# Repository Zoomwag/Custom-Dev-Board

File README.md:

# RP2040 Development Board

---

## Overview

This dev board is based on the Raspberry Pi RP2040 microcontroller that i deigned to learn how MCUS work
---

##  Features

- RP2040 dual-core ARM Cortex-M0+ microcontroller
- USB C interface for power and programming (much better than the picos micro usb)
- GPIO breakout for easy access
- On-board voltage regulation
- Compact and clean PCB layout

---

##  Images

### Schematic

Here you can see the schematic. I tried my best to adhere to good schemtic pratcies and i actually think that i did pretty good.

### PCB Layout

Here we can see the fully routed PCB

### 3D Model

Here you can see a 3d model of the PCB

---

---

##  Getting Started

1. Flash firmware using USB
2. Connect peripherals via GPIO
3. Start building your project

The board can then be programmed in micro python

---

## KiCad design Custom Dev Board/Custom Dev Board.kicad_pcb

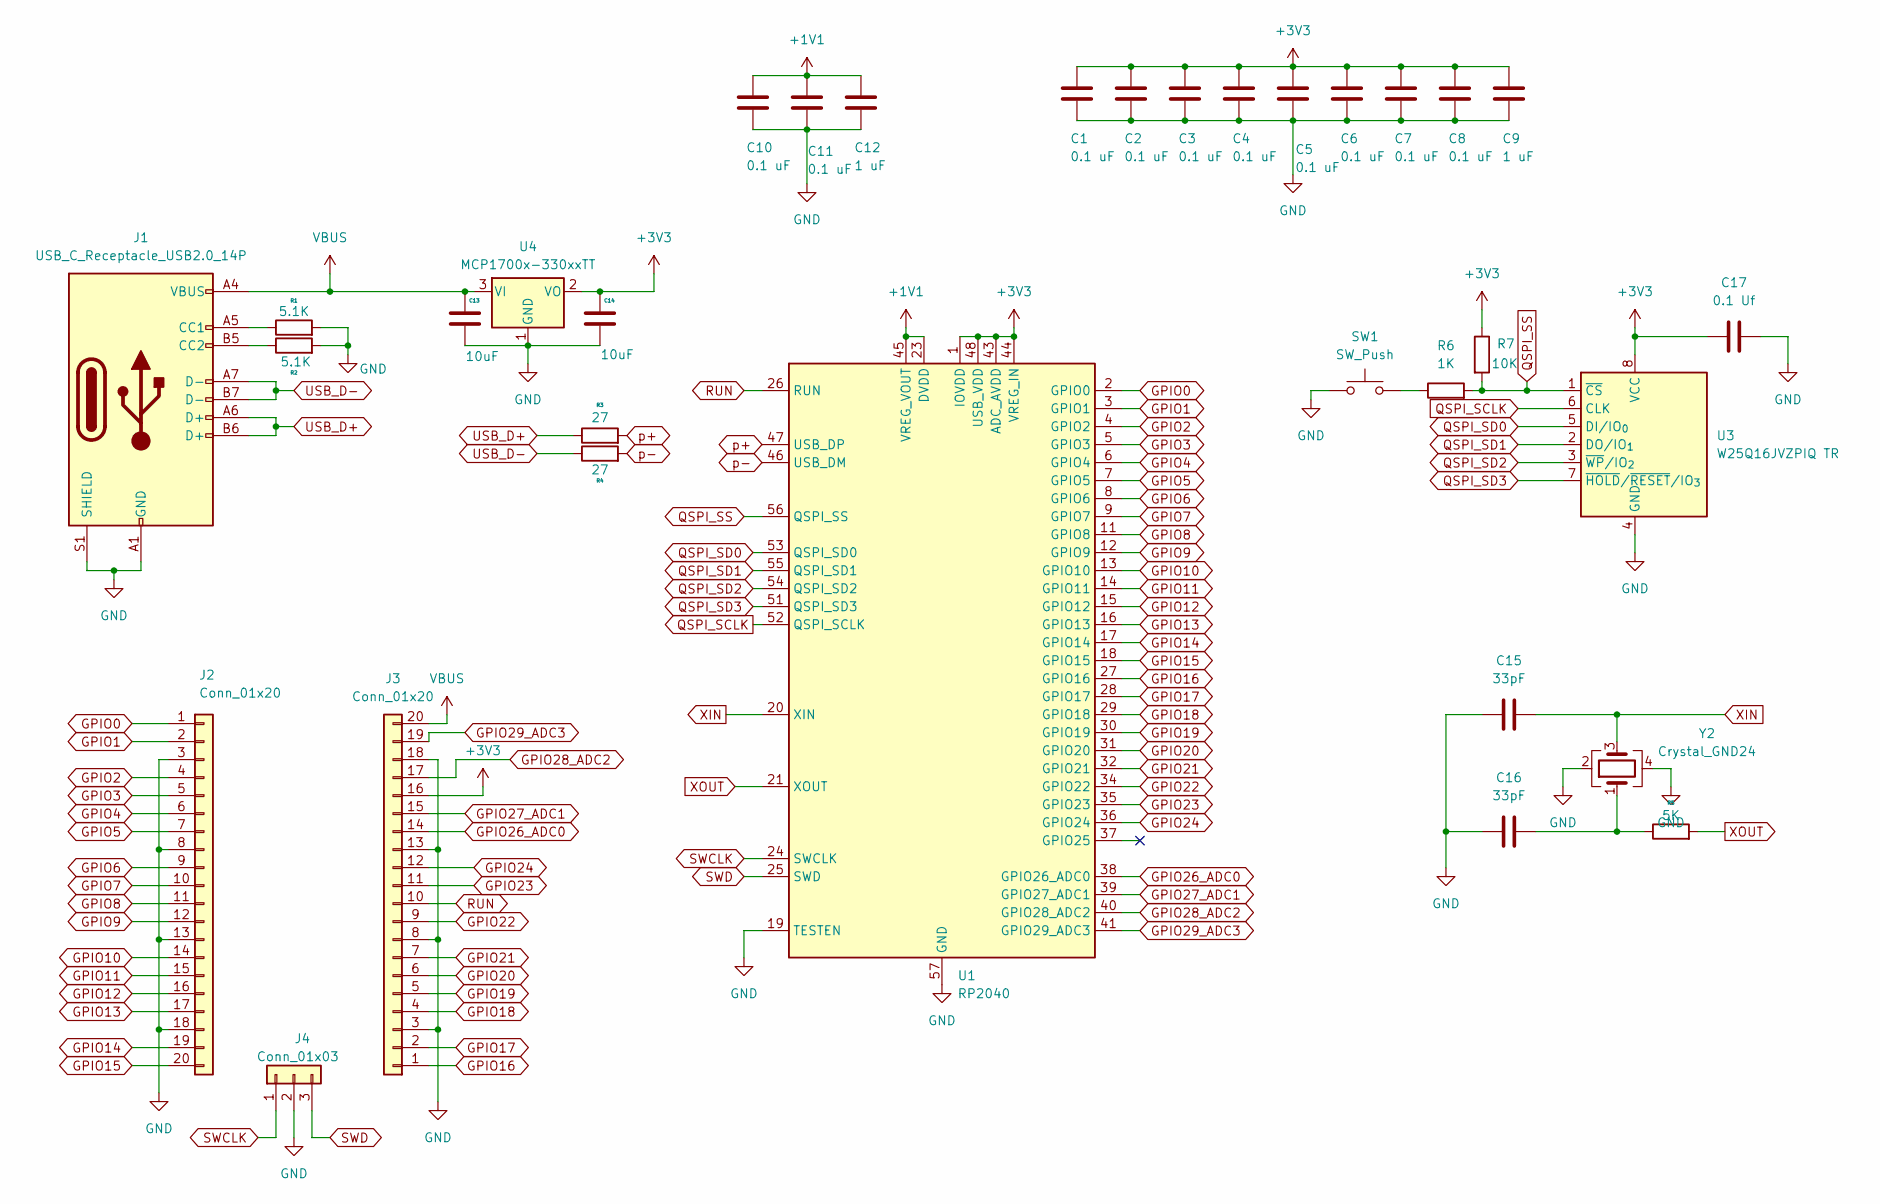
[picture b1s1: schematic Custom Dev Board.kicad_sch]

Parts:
C1, C2, C3, C4, C5, C6, C7, C8, C10, C11: 0.1 uF; C_0402_1005Metric
C9, C12: 1 uF; C_0402_1005Metric
C13, C14: 10uF; C_0603_1608Metric
C15, C16: 33pF; C_0402_1005Metric
C17: 0.1 Uf; C_0402_1005Metric
J1: USB_C_Receptacle_USB2.0_14P; USB_C_Receptacle_HRO_TYPE-C-31-M-12
J2, J3: Conn_01x20; PinHeader_1x20_P2.54mm_Vertical
J4: Conn_01x03; PinHeader_1x03_P2.54mm_Vertical
R1, R2: 5.1K; R_0402_1005Metric
R3, R4: 27; R_0402_1005Metric
R5: 5K; R_0402_1005Metric
R6: 1K; R_0402_1005Metric
R7: 10K; R_0402_1005Metric
SW1: SW_Push; SW_Push_SPST_NO_Alps_SKRK
U1: RP2040; QFN-56-1EP_7x7mm_P0.4mm_EP3.2x3.2mm
U3: W25Q16JVZPIQ TR; Winbond_USON-8-1EP_3x2mm_P0.5mm_EP0.2x1.6mm
U4: MCP1700x-330xxTT; SOT-23
Y2: Crystal_GND24; Crystal_SMD_3225-4Pin_3.2x2.5mm

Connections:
+1V1: C10.1, C11.1, C12.1, U1.23 (DVDD), U1.45 (VREG_VOUT), U1.50 (DVDD)
+3V3: C1.1, C2.1, C3.1, C4.1, C5.1, C6.1, C7.1, C8.1, C9.1, C14.1, C17.1, J3.16, R7.1, U1.1 (IOVDD), U1.10 (IOVDD), U1.22 (IOVDD), U1.33 (IOVDD), U1.42 (IOVDD), U1.43 (ADC_AVDD), U1.44 (VREG_IN), U1.48 (USB_VDD), U1.49 (IOVDD), U3.8 (VCC), U4.2 (VO)
GND: C1.2, C2.2, C3.2, C4.2, C5.2, C6.2, C7.2, C8.2, C9.2, C10.2, C11.2, C12.2, C13.2, C14.2, C15.1, C16.1, C17.2, J1.A1 (GND), J1.A12 (GND), J1.B1 (GND), J1.B12 (GND), J1.S1 (SHIELD), J2.3, J2.8, J2.13, J2.18, J3.3, J3.8, J3.13, J3.18, J4.2, R1.2, R2.2, SW1.1, U1.19 (TESTEN), U1.57 (GND), U3.4 (GND), U4.1 (GND), Y2.2, Y2.4
GPIO0: J2.1, U1.2 (GPIO0)
GPIO1: J2.2, U1.3 (GPIO1)
GPIO2: J2.4, U1.4 (GPIO2)
GPIO3: J2.5, U1.5 (GPIO3)
GPIO4: J2.6, U1.6 (GPIO4)
GPIO5: J2.7, U1.7 (GPIO5)
GPIO6: J2.9, U1.8 (GPIO6)
GPIO7: J2.10, U1.9 (GPIO7)
GPIO8: J2.11, U1.11 (GPIO8)
GPIO9: J2.12, U1.12 (GPIO9)
GPIO10: J2.14, U1.13 (GPIO10)
GPIO11: J2.15, U1.14 (GPIO11)
GPIO12: J2.16, U1.15 (GPIO12)
GPIO13: J2.17, U1.16 (GPIO13)
GPIO14: J2.19, U1.17 (GPIO14)
GPIO15: J2.20, U1.18 (GPIO15)
GPIO16: J3.1, U1.27 (GPIO16)
GPIO17: J3.2, U1.28 (GPIO17)
GPIO18: J3.4, U1.29 (GPIO18)
GPIO19: J3.5, U1.30 (GPIO19)
GPIO20: J3.6, U1.31 (GPIO20)
GPIO21: J3.7, U1.32 (GPIO21)
GPIO22: J3.9, U1.34 (GPIO22)
GPIO23: J3.11, U1.35 (GPIO23)
GPIO24: J3.12, U1.36 (GPIO24)
GPIO26_ADC0: J3.14, U1.38 (GPIO26_ADC0)
GPIO27_ADC1: J3.15, U1.39 (GPIO27_ADC1)
GPIO28_ADC2: J3.17, U1.40 (GPIO28_ADC2)
GPIO29_ADC3: J3.19, U1.41 (GPIO29_ADC3)
unnamed: C16.2, R5.1, Y2.1
unnamed: J1.A5 (CC1), R1.1
unnamed: J1.B5 (CC2), R2.1
unnamed: R6.1, SW1.2
QSPI_SCLK: U1.52 (QSPI_SCLK), U3.6 (CLK)
QSPI_SD0: U1.53 (QSPI_SD0), U3.5 (DI/IO_{0})
QSPI_SD1: U1.55 (QSPI_SD1), U3.2 (DO/IO_{1})
QSPI_SD2: U1.54 (QSPI_SD2), U3.3 (~WP/IO_{2})
QSPI_SD3: U1.51 (QSPI_SD3), U3.7 (~HOLD/~RESET/IO_{3})
QSPI_SS: R6.2, R7.2, U1.56 (QSPI_SS), U3.1 (~CS)
RUN: J3.10, U1.26 (RUN)
SWCLK: J4.1, U1.24 (SWCLK)
SWD: J4.3, U1.25 (SWD)
USB_D+: J1.A6 (D+), J1.B6 (D+), R3.1
USB_D-: J1.A7 (D-), J1.B7 (D-), R4.1
VBUS: C13.1, J1.A4 (VBUS), J1.A9 (VBUS), J1.B4 (VBUS), J1.B9 (VBUS), J3.20, U4.3 (VI)
XIN: C15.2, U1.20 (XIN), Y2.3
XOUT: R5.2, U1.21 (XOUT)
p+: R3.2, U1.47 (USB_DP)
p-: R4.2, U1.46 (USB_DM)

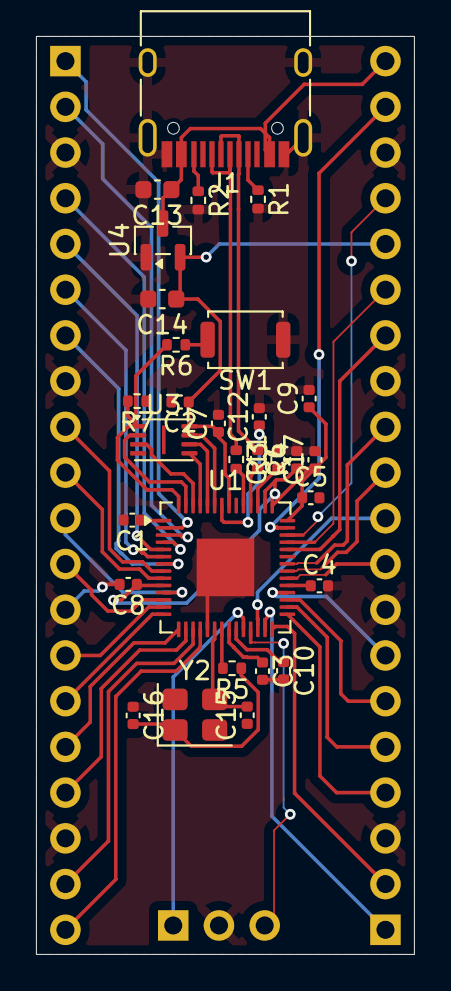
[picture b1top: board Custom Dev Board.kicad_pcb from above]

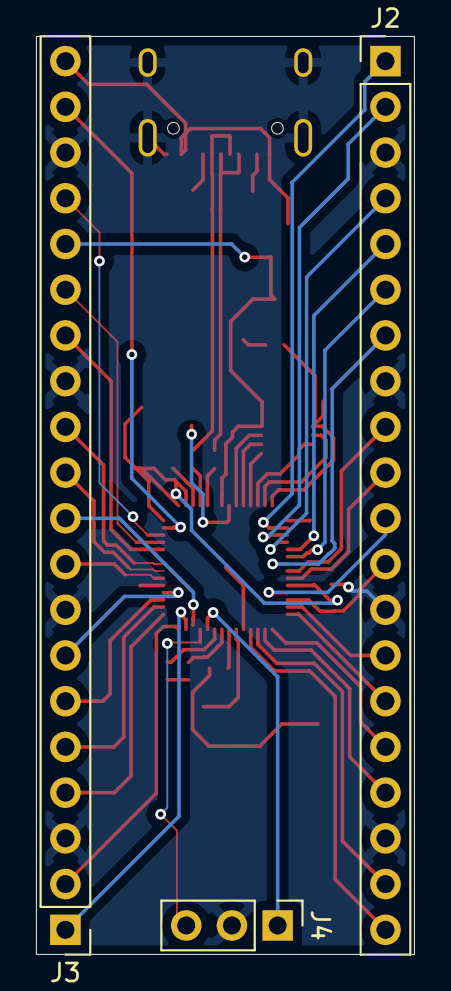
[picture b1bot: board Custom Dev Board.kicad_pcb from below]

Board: 2 copper layers, 21.0 x 51.0 mm, 33 parts (3 on the bottom side), 52 nets.
